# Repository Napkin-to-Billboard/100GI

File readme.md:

**Napkin to Billboard: 25 Gadget Ideas** is an innovative e-book for aspiring inventors, makers, designers and entrepreneurs.

But wait, there's more! Sign up to our free video tutorials and guides on
https://www.youtube.com/@NapkinToBillboard

and visit
https://www.napkintobillboard.com

to join the community and enroll in our courses.

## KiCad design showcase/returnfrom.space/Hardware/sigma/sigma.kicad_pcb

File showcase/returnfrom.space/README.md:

# returnfrom.space Showcase

This directory contains firmware for the **returnfrom.space** showcase project.
Hardware kits can be obtained from [returnfrom.space](https://returnfrom.space).
The project now also ships a `Hardware` folder containing KiCad design files for
the boards.

Edit the firmware using [Thonny](https://thonny.org/) and upload it to the boards.

## Boards

- **Console** &mdash; RP2040 based. Configured as a USB keyboard with 16 tactile
  switches. Provides UART output at 115200&nbsp;bps.
- **SEB** &mdash; ESP32-S2 based. Includes drivers for an SSD1306 display, DAC and
  ADC sampled at 8&nbsp;kHz, with UART input.
- **Sigma** &mdash; ESP32-S2 based. Similar to SEB with its own pin mappings and
  peripherals.

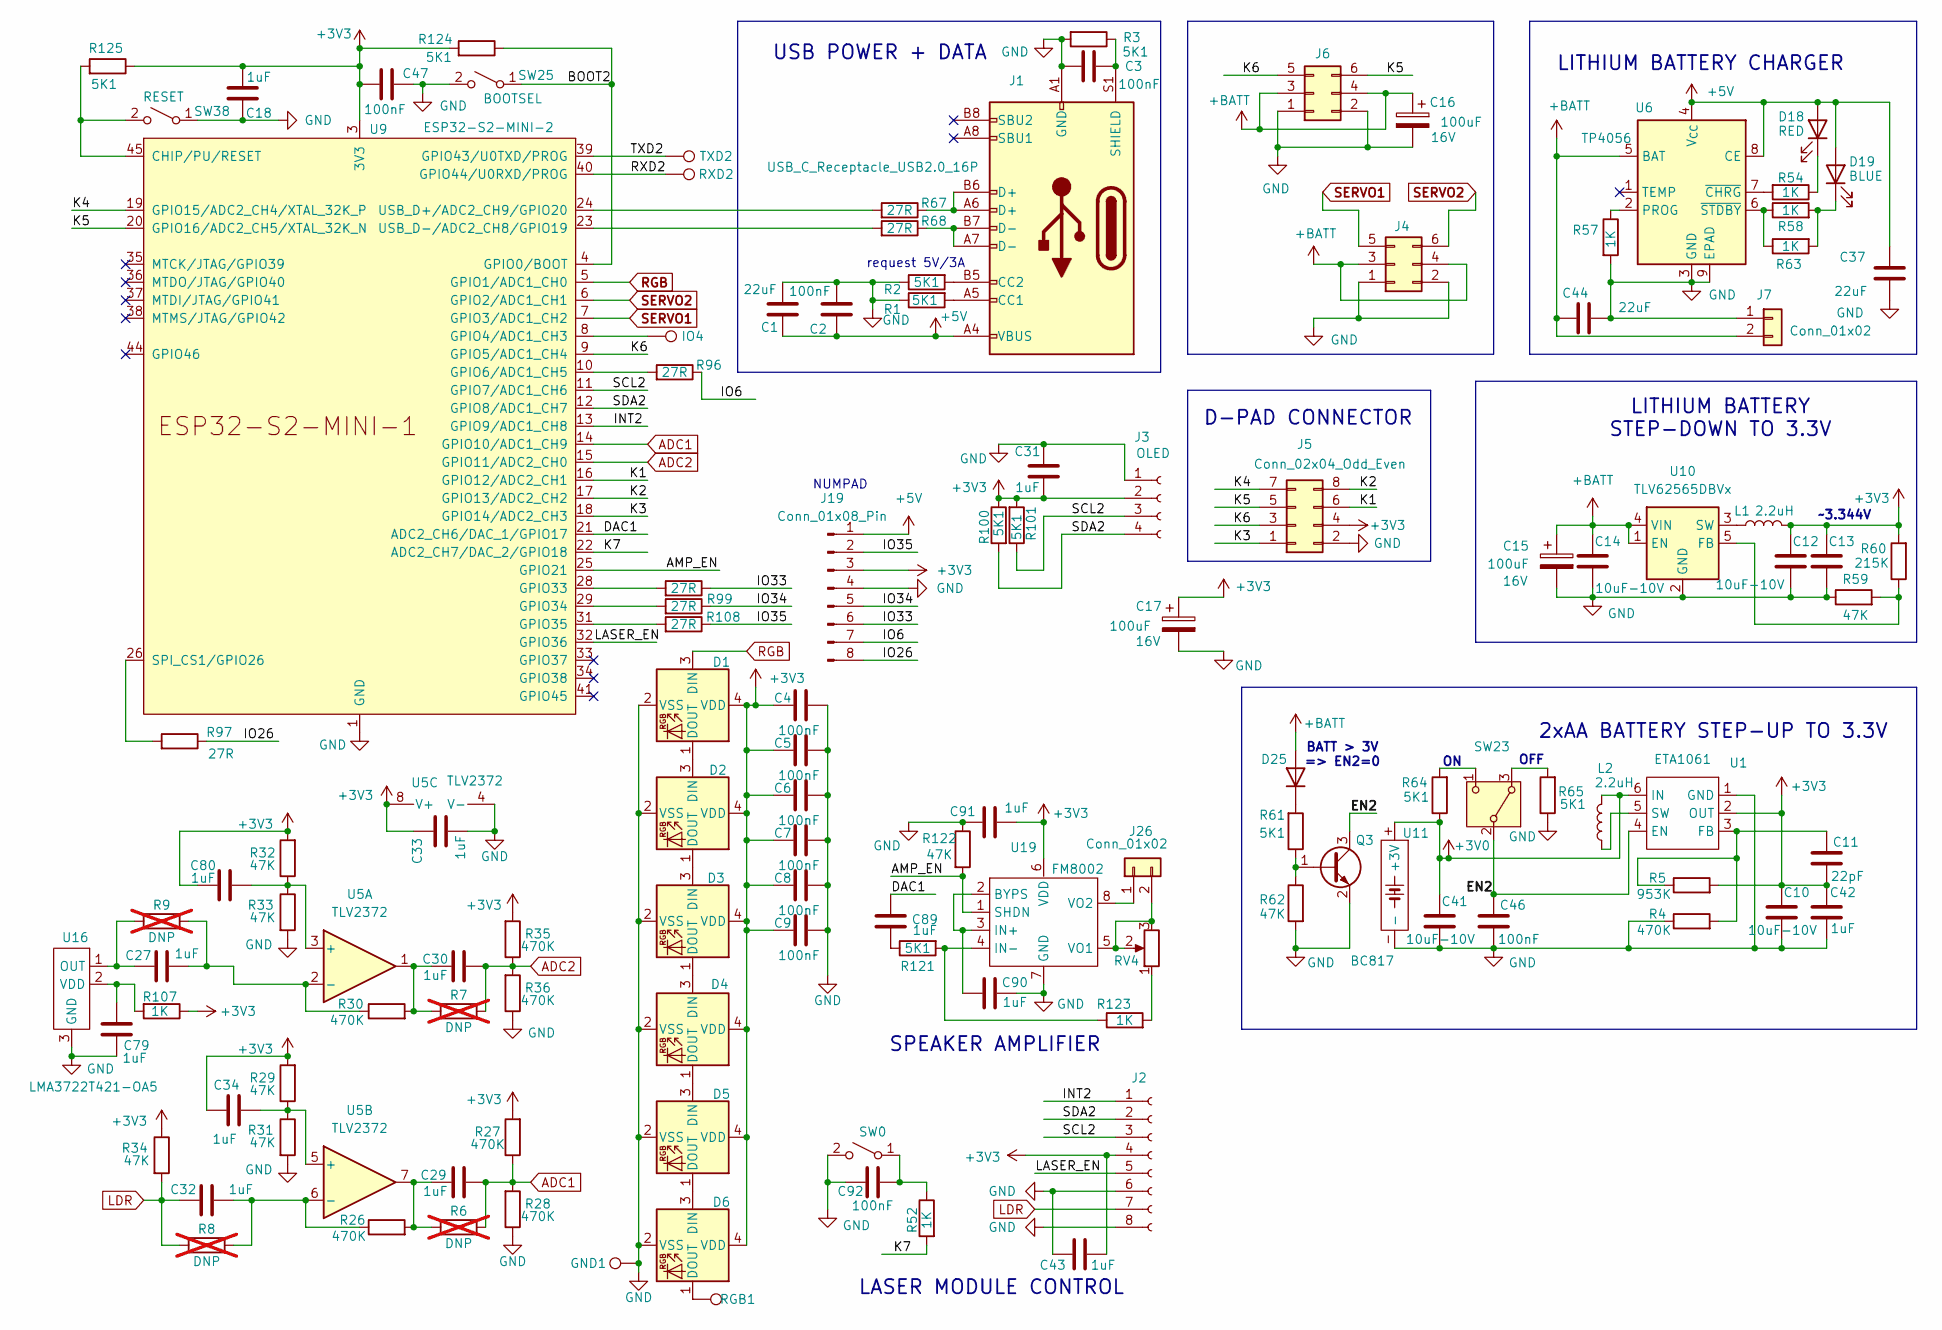
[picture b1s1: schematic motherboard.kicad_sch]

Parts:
C1, C37, C44: 22uF; C_0805_2012Metric
C2, C3, C4, C5, C6, C7, C8, C9, C46, C47, C92: 100nF; C_0402_1005Metric
C10, C12, C13, C14, C41: 10uF-10V; C_0603_1608Metric
C11: 22pF; C_0402_1005Metric
C15, C16, C17: 100uF; CP_Elec_6.3x5.4; Voltage 16V
C18, C27, C29, C30, C31, C32, C33, C34, C42, C43, C79, C80, C89, C90, C91: 1uF; C_0402_1005Metric
D1, D2, D3, D4, D5, D6: WS2812B-2020; LED_WS2812B-2020_PLCC4_2.0x2.0mm
D18: RED; LED_0603_1608Metric
D19: BLUE; LED_0603_1608Metric
D25: D; D_SOD-323
GND1: TestPoint; TestPoint_Pad_D2.0mm
IO4: TestPoint; TestPoint_Pad_D2.0mm
J1: USB_C_Receptacle_USB2.0_16P; USB_C_Receptacle_HCTL_HC-TYPE-C-16P-01A
J2: Conn_01x08_Socket; TE_0-1734839-8_1x08-1MP_P0.5mm_Horizontal
J3: OLED; Display_128x64_096_I2C
J4, J6: Conn_02x03_Odd_Even; PinHeader_2x03_P2.54mm_Horizontal
J5: Conn_02x04_Odd_Even; PinHeader_2x04_P2.54mm_Vertical
J7, J26: Conn_01x02; Hirose_DF13-02P-1.25DS_1x02_P1.25mm_Horizontal
J19: Conn_01x08_Pin; PinHeader_1x08_P2.54mm_Horizontal
L1, L2: 2.2uH; L_Cenker_CKCS201610
Q3: BC817; SOT-23
R1, R2, R3, R61, R64, R65, R100, R101, R121, R124, R125: 5K1; R_0402_1005Metric
R4, R26, R27, R28, R30, R35, R36: 470K; R_0402_1005Metric
R5: 953K; R_0402_1005Metric
R6, R7, R8, R9: DNP; R_0402_1005Metric; not fitted
R29, R31, R32, R33, R34, R59, R62, R122: 47K; R_0402_1005Metric
R52, R54, R57, R58, R63, R107, R123: 1K; R_0402_1005Metric
R60: 215K; R_0402_1005Metric
R67, R68, R96, R97, R98, R99, R108: 27R; R_0402_1005Metric
RGB1: TestPoint; TestPoint_Pad_D2.0mm
RV4: R_Potentiometer; Potentiometer_Runtron_RM-065_Vertical
RXD2: TestPoint; TestPoint_Pad_D2.0mm
SW0: SW_SPST; SW_PUSH-12mm
SW23: SW_SPDT_321; SW_Slide_SPDT_Angled_CK_OS102011MA1Q
SW25: BOOTSEL; SW_SPST_TL3305C
SW38: RESET; SW_SPST_TL3305C
TXD2: TestPoint; TestPoint_Pad_D2.0mm
U1: ETA1061; DFN-6-1EP_2x2mm_P0.65mm_EP1.01x1.7mm
U5: TLV2372; SOIC-8_3.9x4.9mm_P1.27mm
U6: TP4056; SOIC-8-1EP_3.9x4.9mm_P1.27mm_EP2.41x3.3mm_ThermalVias
U9: ESP32-S2-MINI-2; ESP32-S2-MINI-1
U10: TLV62565DBVx; SOT-23-5
U11: 2xAA
U16: LMA3722T421-OA5; LMA3722T421
U19: FM8002; SOIC-8_3.9x4.9mm_P1.27mm

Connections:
+3V0: C41.1, L2.2, R64.1, U1.6 (IN), U11.+ (+3V)
+3V3: C4.2, C5.2, C6.2, C7.2, C8.2, C9.2, C10.1, C11.1, C12.1, C13.1, C17.1, C18.2, C31.2, C33.2, C34.1, C42.1, C43.2, C47.2, C80.1, C91.2, D1.4 (VDD), D2.4 (VDD), D3.4 (VDD), D4.4 (VDD), D5.4 (VDD), D6.4 (VDD), J2.4, J3.2, J5.4, J19.3, L1.2, R5.2, R27.2, R29.2, R32.2, R34.1, R35.2, R60.2, R100.1, R101.2, R107.1, R124.2, R125.1, U1.2 (OUT), U5.8 (V+), U9.3 (3V3), U19.6 (VDD)
+5V: C1.1, C2.1, C37.1, D18.2 (A), D19.2 (A), J1.A4 (VBUS), J1.A9 (VBUS), J1.B4 (VBUS), J1.B9 (VBUS), J19.1, U6.4 (V_{CC}), U6.8 (CE)
+BATT: C14.1, C15.1, C16.1, C44.1, D25.2 (A), J4.3, J4.4, J6.3, J6.4, J7.2, U6.5 (BAT), U10.1 (EN), U10.4 (VIN)
/motherboard/AMP_EN: R122.2, U9.25 (GPIO21), U19.1 (SHDN)
/motherboard/BOOT2: R124.1, SW25.1 (A), U9.4 (GPIO0/BOOT)
/motherboard/DAC1: C89.2, U9.21 (ADC2_CH6/DAC_1/GPIO17)
/motherboard/EN2: C46.2, Q3.3 (C), SW23.2 (B), U1.4 (EN)
/motherboard/INT2: J2.1, U9.13 (GPIO9/ADC1_CH8)
/motherboard/IO6: J19.7, R96.1
/motherboard/IO26: J19.8, R97.1
/motherboard/IO33: J19.6, R98.1
/motherboard/IO34: J19.5, R99.1
/motherboard/IO35: J19.2, R108.1
/motherboard/K1: J5.6, U9.16 (GPIO12/ADC2_CH1)
/motherboard/K2: J5.8, U9.17 (GPIO13/ADC2_CH2)
/motherboard/K3: J5.1, U9.18 (GPIO14/ADC2_CH3)
/motherboard/K4: J5.7, U9.19 (GPIO15/ADC2_CH4/XTAL_32K_P)
/motherboard/K5: J5.5, J6.6, U9.20 (GPIO16/ADC2_CH5/XTAL_32K_N)
/motherboard/K6: J5.3, J6.5, U9.9 (GPIO5/ADC1_CH4)
/motherboard/K7: R52.2, U9.22 (ADC2_CH7/DAC_2/GPIO18)
/motherboard/LASER_EN: J2.5, U9.32 (GPIO36)
/motherboard/RXD2: RXD2.1, U9.40 (GPIO44/U0RXD/PROG)
/motherboard/SCL2: J2.3, J3.3, R101.1, U9.11 (GPIO7/ADC1_CH6)
/motherboard/SDA2: J2.2, J3.4, R100.2, U9.12 (GPIO8/ADC1_CH7)
/motherboard/TXD2: TXD2.1, U9.39 (GPIO43/U0TXD/PROG)
ADC1: C29.2, R6.2, R27.1, R28.2, U9.14 (GPIO10/ADC1_CH9)
ADC2: C30.2, R7.2, R35.1, R36.2, U9.15 (GPIO11/ADC2_CH0)
GND: C1.2, C2.2, C3.2, C4.1, C5.1, C6.1, C7.1, C8.1, C9.1, C10.2, C12.2, C13.2, C14.2, C15.2, C16.2, C17.2, C18.1, C31.1, C33.1, C37.2, C41.2, C42.2, C43.1, C44.2, C46.1, C47.1, C79.1, C90.2, C91.1, C92.2, D1.2 (VSS), D2.2 (VSS), D3.2 (VSS), D4.2 (VSS), D5.2 (VSS), D6.2 (VSS), GND1.1, J1.A1 (GND), J1.A12 (GND), J1.B1 (GND), J1.B12 (GND), J2.6, J2.8, J3.1, J4.1, J4.2, J5.2, J6.1, J6.2, J7.1, J19.4, Q3.2 (E), R1.1, R2.1, R3.2, R4.1, R28.1, R31.2, R33.2, R36.1, R57.2, R59.1, R62.2, R65.1, R122.1, SW0.2 (B), SW25.2 (B), SW38.1 (A), U1.1 (GND), U1.7 (GND), U5.4 (V-), U6.3 (GND), U6.9 (EPAD), U9.1 (GND), U9.2 (GND), U9.30 (GND), U9.42 (GND), U9.43 (GND), U9.46 (GND), U9.47 (GND), U9.48 (GND), U9.49 (GND), U9.50 (GND), U9.51 (GND), U9.52 (GND), U9.53 (GND), U9.54 (GND), U9.55 (GND), U9.56 (GND), U9.57 (GND), U9.58 (GND), U9.59 (GND), U9.60 (GND), U9.61 (GND), U9.62 (GND), U9.63 (GND), U9.64 (GND), U9.65 (GND), U10.2 (GND), U11.-, U16.3 (GND), U16.4 (GND), U19.7 (GND)
LDR: C32.1, J2.7, R8.1, R34.2
unnamed: C29.1, R6.1, R26.2, U5.7
unnamed: C30.1, R7.1, R30.2, U5.1
unnamed: C89.1, R121.1
unnamed: D1.1 (DOUT), D2.3 (DIN)
unnamed: D2.1 (DOUT), D3.3 (DIN)
unnamed: D3.1 (DOUT), D4.3 (DIN)
unnamed: D4.1 (DOUT), D5.3 (DIN)
unnamed: D5.1 (DOUT), D6.3 (DIN)
unnamed: D6.1 (DOUT), RGB1.1
unnamed: D18.1 (K), R54.1
unnamed: D19.1 (K), R58.2, R63.2
unnamed: D25.1 (K), R61.2
unnamed: J1.A5 (CC1), R1.2
unnamed: J1.B5 (CC2), R2.2
unnamed: J1.A6 (D+), J1.B6 (D+), R67.1
unnamed: J1.A7 (D-), J1.B7 (D-), R68.1
unnamed: C3.1, J1.S1 (SHIELD), R3.1
unnamed: J26.1, U19.8 (VO2)
unnamed: J26.2, RV4.2, RV4.3, U19.5 (VO1)
unnamed: Q3.1 (B), R61.1, R62.1
unnamed: R123.2, RV4.1
unnamed: C92.1, R52.1, SW0.1 (A)
unnamed: R65.2, SW23.3 (A)
unnamed: R64.2, SW23.1 (C)
unnamed: R125.2, SW38.2 (B), U9.45 (CHIP/PU/RESET)
unnamed: C11.2, R4.2, R5.1, U1.3 (FB)
unnamed: L2.1, U1.5 (SW)
unnamed: C80.2, R32.1, R33.1, U5.3 (+)
unnamed: C27.2, R9.2, R30.1, U5.2 (-)
unnamed: C34.2, R29.1, R31.1, U5.5 (+)
unnamed: C32.2, R8.2, R26.1, U5.6 (-)
unnamed: R57.1, U6.2 (PROG)
unnamed: R54.2, U6.7 (~CHRG)
unnamed: R58.1, R63.1, U6.6 (~STDBY)
unnamed: IO4.1, U9.8 (GPIO4/ADC1_CH3)
unnamed: R96.2, U9.10 (GPIO6/ADC1_CH5)
unnamed: R98.2, U9.28 (GPIO33)
unnamed: R99.2, U9.29 (GPIO34)
unnamed: R108.2, U9.31 (GPIO35)
unnamed: R97.2, U9.26 (SPI_CS1/GPIO26)
unnamed: R67.2, U9.24 (USB_D+/ADC2_CH9/GPIO20)
unnamed: R68.2, U9.23 (USB_D-/ADC2_CH8/GPIO19)
unnamed: R59.2, R60.1, U10.5 (FB)
unnamed: L1.1, U10.3 (SW)
unnamed: C27.1, R9.1, U16.1 (OUT)
unnamed: C79.2, R107.2, U16.2 (VDD)
unnamed: C90.1, U19.2 (BYPS), U19.3 (IN+)
unnamed: R121.2, R123.1, U19.4 (IN-)
RGB: D1.3 (DIN), U9.5 (GPIO1/ADC1_CH0)
SERVO1: J4.5, U9.7 (GPIO3/ADC1_CH2)
SERVO2: J4.6, U9.6 (GPIO2/ADC1_CH1)

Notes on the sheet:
OFF
BATT > 3V => EN2=0
LITHIUM BATTERY STEP-DOWN TO 3.3V
2xAA BATTERY STEP-UP TO 3.3V
NUMPAD
request 5V/3A
USB POWER + DATA
LITHIUM BATTERY CHARGER
LASER MODULE CONTROL
D-PAD CONNECTOR
~3.344V
SPEAKER AMPLIFIER

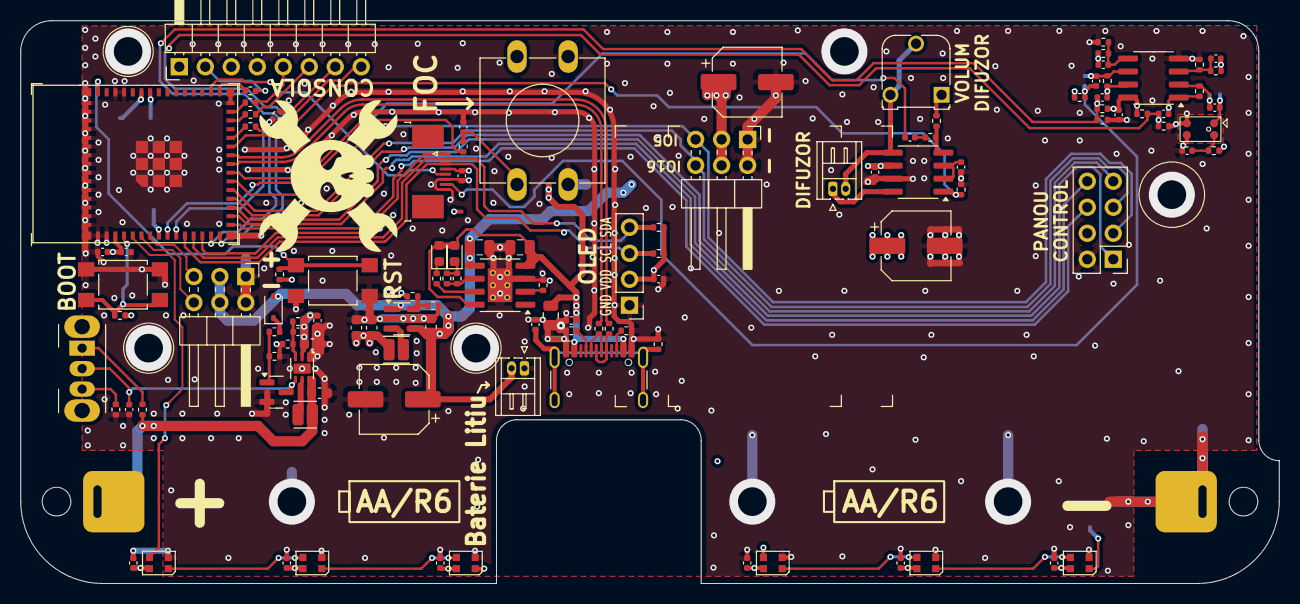
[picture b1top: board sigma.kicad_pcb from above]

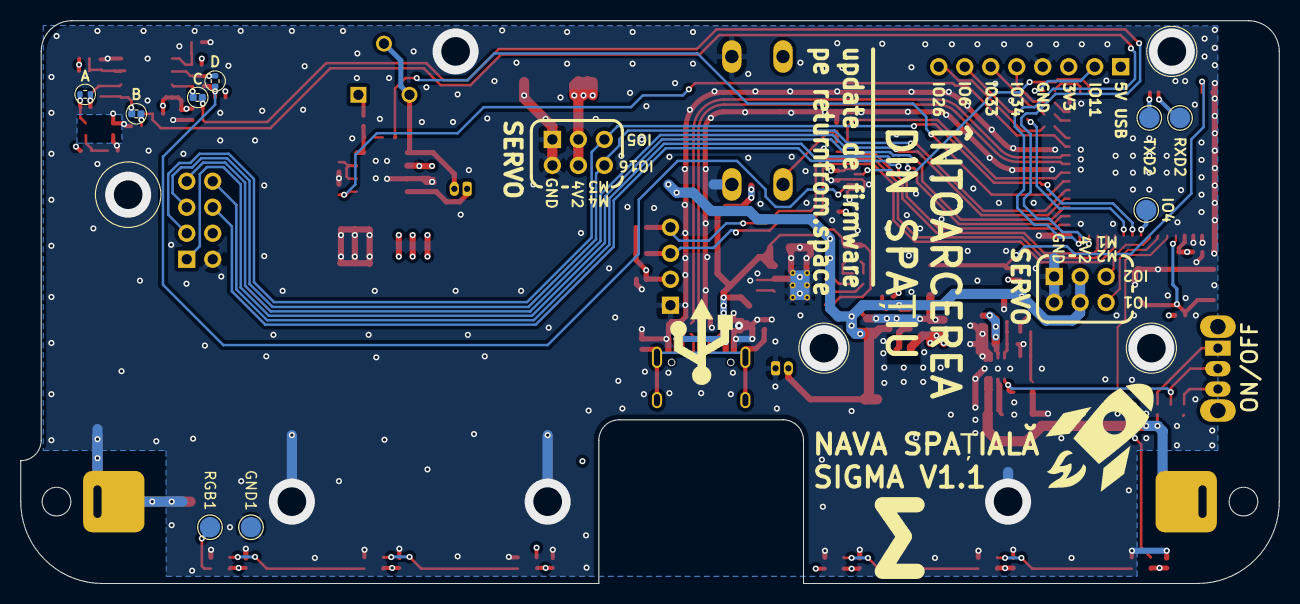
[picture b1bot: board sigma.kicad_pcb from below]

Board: 4 copper layers, 123.0 x 55.0 mm, 123 parts (9 on the bottom side), 81 nets.

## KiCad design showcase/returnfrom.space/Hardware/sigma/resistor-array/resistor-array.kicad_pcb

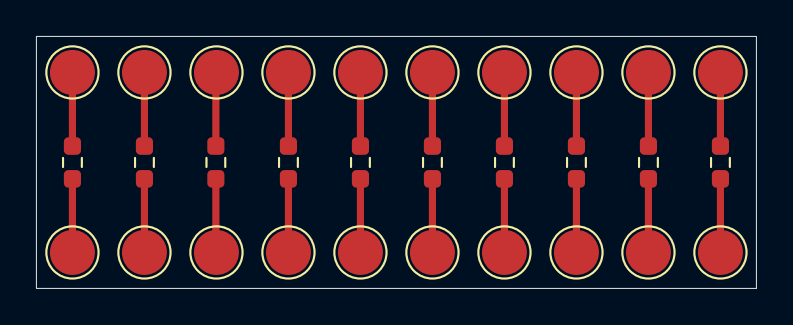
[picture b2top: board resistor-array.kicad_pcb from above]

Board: 2 copper layers, 40.0 x 14.0 mm, 30 parts (0 on the bottom side), 20 nets.

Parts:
R1, R2, R3, R4, R5, R6, R7, R8, R9, R10: R; R_0603_1608Metric_Pad0.98x0.95mm_HandSolder
TP1, TP2, TP3, TP4, TP5, TP6, TP7, TP8, TP9, TP10, TP11, TP12, TP13, TP14, TP15, TP16, TP17, TP18, TP19, TP20: TestPoint; TestPoint_Pad_D2.5mm

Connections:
unnamed: R1.1, TP1.1
unnamed: R1.2, TP11.1
unnamed: R2.1, TP2.1
unnamed: R2.2, TP12.1
unnamed: R3.1, TP3.1
unnamed: R3.2, TP13.1
unnamed: R4.1, TP4.1
unnamed: R4.2, TP14.1
unnamed: R5.1, TP5.1
unnamed: R5.2, TP15.1
unnamed: R6.1, TP6.1
unnamed: R6.2, TP16.1
unnamed: R7.1, TP7.1
unnamed: R7.2, TP17.1
unnamed: R8.1, TP8.1
unnamed: R8.2, TP18.1
unnamed: R9.1, TP9.1
unnamed: R9.2, TP19.1
unnamed: R10.1, TP10.1
unnamed: R10.2, TP20.1

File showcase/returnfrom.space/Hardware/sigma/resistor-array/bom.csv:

Designator,Footprint,Quantity,Value,LCSC Part #
"TP1, TP10, TP11, TP12, TP13, TP14, TP15, TP16, TP17, TP18, TP19, TP2, TP20, TP3, TP4, TP5, TP6, TP7, TP8, TP9",2mm-pogo,20,TestPoint,
R1,R0603,1,R,
R2,R0603,1,,
R3,R0603,1,,
R4,R0603,1,,
R5,R0603,1,,
R6,R0603,1,,
R7,R0603,1,,
R8,R0603,1,,
R9,R0603,1,,
R10,R0603,1,,

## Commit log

2025-03-12 Create LICENSE
2025-06-05 Improve Console HID keyboard example
2025-06-05 Rename Delta board to Sigma
2025-06-05 added electronics
2025-06-05 added step files
2025-06-05 Update console keypad scanning and docs
2025-06-15 board almost done
2025-06-18 panelizing...
2025-06-19 Done. Ordered 50pcs. TO DO: clean-up, add BOM & POS
2026-01-27 improved (bugfixed) sigma board
2026-01-31 sigma fix - not validated
